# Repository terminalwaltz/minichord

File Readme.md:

# minichord 

This repository contains the source file both for the minichord itself and its documentation. 

To be informed about the project, please subscribe to [the newsletter](https://buttondown.com/BenjaminPoilve).

* [#1 project update](https://buttondown.com/BenjaminPoilve/archive/minichord-update-1/) 
* [#2 project update](https://buttondown.com/BenjaminPoilve/archive/minichord-update-2/) 
* [#3 project update and pre-order link](https://buttondown.com/BenjaminPoilve/archive/minichord-update-3/) 
* [#4 project update](https://buttondown.com/BenjaminPoilve/archive/minichord-update-4/) 
* [#5 project update](https://buttondown.com/BenjaminPoilve/archive/minichord-update-5/) 

## Documentation 

The best way to get to know this project is to visit the [minichord website](https://minichord.com/) which contains the documentation of the project. 

In particular it contains:

- the [user manual of the minichord](https://minichord.com/user_manual/)
- the [assembly guide of the minichord](https://minichord.com/assembly/)

This documentation is build with mkdocs and the relevant source and build script is available in the [documentation folder](https://github.com/BenjaminPoilve/MiniChord/tree/main/documentation).

## Hardware 

The hardware folder contains the necessary ressources to build a minichord. 

All hardware is provided under a Creative Commons Attribution-NonCommercial 4.0 International Public
License (CC BY-NC 4.0). 

In particular it contains: 

- the [files necessary to manufacture the PCB](https://github.com/BenjaminPoilve/MiniChord/tree/main/hardware/PCB)
- the [full BOM of the project](https://github.com/BenjaminPoilve/MiniChord/tree/main/hardware/BOM)
- the [3D enclosure files](https://github.com/BenjaminPoilve/MiniChord/tree/main/hardware/3D/rendering)
- the [keycap routing files](https://github.com/BenjaminPoilve/MiniChord/tree/main/hardware/graphics)

## Firmware 

The firmware folder contains the project firmware and necessary programming ressources.

All software is provided under a 3-clause BSD License.

In particular it contains: 
- the [Hex firmware](https://github.com/BenjaminPoilve/MiniChord/blob/main/firmware/firmware.hex)
- the full [PlatformIO project](https://github.com/BenjaminPoilve/MiniChord/tree/main/firmware)
- the [minicontrol software](https://github.com/BenjaminPoilve/MiniChord/tree/main/firmware/minicontrol)

## Media 

Here is a list of available media related to the project (to be completed) :

- a technical video about [the minicontrol system](https://www.youtube.com/watch?v=h-6qkhU_WoA&t=933s)
- a short [audio demo of selected presets](https://minichord.com/ressources/audio_demo.mp3)

## Contact 

For any information about the project, don't hesitate to write at info@minichord.com

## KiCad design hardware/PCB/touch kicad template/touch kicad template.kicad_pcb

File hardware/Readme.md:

# Hardware  

This folder contains the necessary ressources to build a minichord. 

### Electronics

* [Main PCB schematics](https://github.com/BenjaminPoilve/MiniChord/blob/main/hardware/PCB/miniChord_main_PCB/MiniChord.pdf)
* [Main PCB Gerber file](https://github.com/BenjaminPoilve/MiniChord/tree/main/hardware/PCB/miniChord_main_PCB/gerber)
* [Touch zone PCB schematics](https://github.com/BenjaminPoilve/MiniChord/blob/main/hardware/PCB/touch%20zones/default%20touch%20PCB/touch_zone.pdf)
* [Touch zone PCB Gerber file](https://github.com/BenjaminPoilve/MiniChord/blob/main/hardware/PCB/touch%20zones/default%20touch%20PCB/gerber)
* [Template for custom touch zone](https://github.com/BenjaminPoilve/MiniChord/blob/main/hardware/PCB/touch%20zones/touch%20kicad%20template)

### BOM

* [Full BOM](https://github.com/BenjaminPoilve/MiniChord/blob/main/hardware/BOM/full_BOM.pdf)

### 3D files

* [Bottom shell](https://github.com/BenjaminPoilve/MiniChord/blob/main/hardware/3D/rendering/render_v9_bottom.scad.stl) 
* [Top shell](https://github.com/BenjaminPoilve/MiniChord/blob/main/hardware/3D/rendering/render_v9_top1_5.scad.stl)

### 2D files 

* [Key engraving](https://github.com/BenjaminPoilve/MiniChord/blob/main/hardware/graphics/key_engraving.svg)

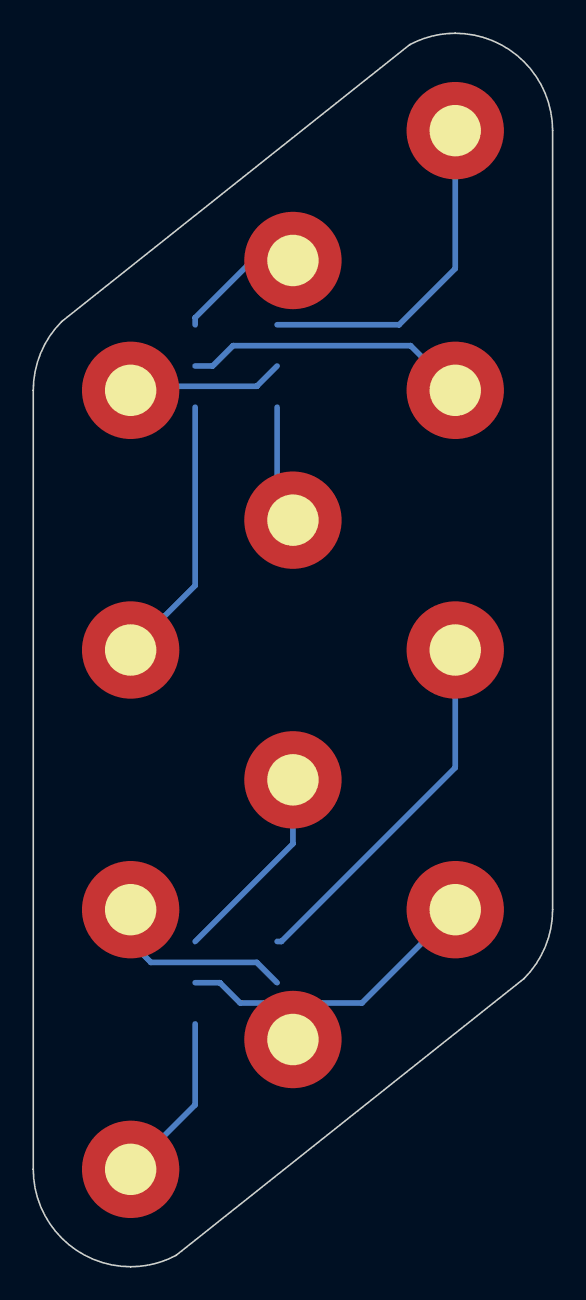
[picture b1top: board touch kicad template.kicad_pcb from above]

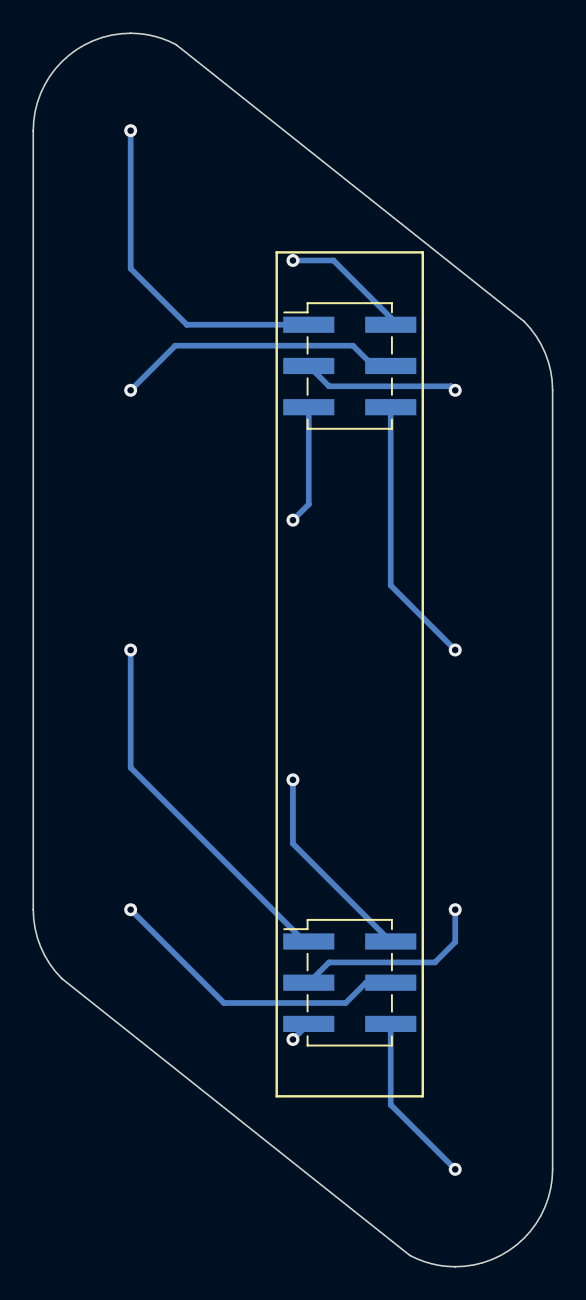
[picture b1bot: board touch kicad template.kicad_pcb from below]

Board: 2 copper layers, 32.0 x 76.0 mm, 14 parts (2 on the bottom side), 12 nets.

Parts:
J1, J2: Conn_02x03_Top_Bottom; PinHeader_2x03_P2.54mm_Vertical_SMD
T1, T2, T3, T4, T5, T6, T7, T8, T9, T10, T11, T12: Conn_01x01_Male; rond_touch_zone

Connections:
unnamed: J1.1, T1.1
unnamed: J1.2, T3.1
unnamed: J1.3, T5.1
unnamed: J1.4, T2.1
unnamed: J1.5, T4.1
unnamed: J1.6, T6.1
unnamed: J2.1, T7.1
unnamed: J2.2, T9.1
unnamed: J2.3, T11.1
unnamed: J2.4, T8.1
unnamed: J2.5, T10.1
unnamed: J2.6, T12.1

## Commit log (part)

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2024-12-26 Additional 3D files, plus
2024-12-26 Added ressources, fixed typo
2024-12-26 Need to clean file uploaded
2024-12-26 fixed a slight bug with regard to pot secondary functions after preset change (caused the pot to updateat the first # selection)
2024-12-30 Small updates and file cleaning
2025-01-07 Added better logging on minicontrol to help diagnose Shiftr's issue
2025-01-08 Made minicontrol windows-compliant and more robust to deconnnections
2025-01-08 Cleaned the connection logic for minicontrol
2025-01-09 Finally tracked down the issue: Dutch locale changing port into poort. Let's be more souple
2025-01-17 Modified firmware for the 10 minichords: better preset, and fixed reverb noise issue
2025-01-17 Updated documentations for new enclosure that necessitates less manual intervention and cutting. Also fixed an error pointed out by Zach
2025-01-17 Annd forgot to build the site
2025-01-17 Better resolution
2025-02-03 Forgot to reactivate the low battery blinking
2025-02-04 Test to try to solve issue #10
2025-02-07 Added Kicad template for custom touch zone
2025-02-07 A bit of housekeeping
2025-02-07 Midi Sync in feature, as requested in #11
2025-02-09 Update on the webpage to reflect the current status of the projetc (production TBD)
2025-02-11 Commiting new homepage
2025-02-11 A bit better design
2025-02-11 hopefully last fix
2025-02-14 at the request of instalinu, added an electronic BOM with MFR#
2025-02-16 Added battery check at startup plus slight deepening of the screw holes
2025-02-17 Changed the touch zone size following Hainbach's feedback
2025-02-17 Added the newsletter issue #2
2025-02-27 Added step rendering
2025-04-11 PCB update to add the diodes
2025-04-11 Latext compile of the firmware
2025-04-11 update doc to acknowledge release
2025-04-11 Better with a break
2025-05-06 Updated PNG of schematics
2025-05-13 Update to reflect the fact that when testing led can be both color
2025-05-23 added chromatic harp flag
2025-06-06 Solve for issue #23 and #22. Had to add a version identifier to avoid user wondering why some control would not work for their version of the firmware.
2025-06-06 Added function for #20.
2025-06-06 Solved issue #21. Could not preserve preset compatibility, need to add a step to wipe preset after software update
2025-06-06 New firmware and new minicontrol interface to take changes into account
2025-06-06 Ressources
2025-06-08 Added documentation on the arrow per #28, plus limited the range of the retrigger release in the frontend per #31 until I can find a better fix
2025-06-13 Reformated the js to have a separate module for minichord interaction. Added a new test page for preset sharing.
2025-06-13 Forgot to build the doc
2025-06-13 Fix for error #29, detecting the loss of USB connection
2025-06-13 new firmware with mods
2025-06-13 Fix for a regression that took the reverb to a very low level
2025-06-15 New updates on the minishop page
2025-06-15 Add underline to parameter name for more legibility
2025-06-15 fixing manual error identified in #32
2025-06-16 Cleanup before PR study
2025-06-16 Fixed for retrocompatibility plus added forgotten JSON modifications
2025-06-18 Added the Barry Harris preset
2025-06-19 Added new issues of the newsletter
2025-06-20 Added feature requested by #25
2025-06-20 Allows global transposition downwards through some dirty math functions (mapNegativeTransposition). Makes changes to handlechange function. Shouldn't break existing presets.
2025-06-22 Fixes loss of MIDI CH2 output when harp pot is set to zero
2025-06-22 Fixes loss of MIDI CH2 output when harp pot is set to zero. Now with firmware.hex to match.
2025-06-24 add 3d files for keycaps
2025-06-25 Added a bit of volume for the transient
2025-06-25 Fixed #42 by removing arbitrary waveforms
2025-06-25 And the
2025-06-25 Here is the new firmware
2025-06-29 Added latest submitted presets
2025-06-30 Adds single/double tap functions to the sharp button. Currently wired for leslie b3, needs parameter assignments, json entries.
2025-07-03 Adds 'chord frame shift' at address 18. Octave array is the reverse of what would be expected, but it works
2025-07-03 Adds JSON entry
2025-07-03 Adds firmware.hex
2025-07-03 Fixing outdated files, bad at GitHub
2025-07-03 Added John's great presets
2025-07-03 added more docs and videos
2025-07-03 Added minishop reference in minicontrol
2025-07-03 Adds 'chord frame shift' at address 18
2025-07-05 Some new presets from Terminalwaltz
2025-07-08 Adds special harp array for Barry Harris mode with a keymaster
2025-07-08 Fixes my presets; my custom firmwareand/or minicontrol experiment added pitch bends unintentionally. I'll be more careful in the future!
2025-07-08 Remove "chord frame shift" from parameters.json
    I promise I will get better at this. Tried to amend from the command line, but I'm missing something clearly. Obviously this is an artifact from another feature, not meant to have altered the JSON fo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
2025-07-08 Adds special harp array for Barry Harris mode with a Keymaster touchplate.
2025-07-10 Adds Chord Frame Shift, with 2D root_button array. Firmware.hex, JSON change, sysex_handler change, address 18
2025-07-10 Forgot to run generator.py
2025-07-11 A new array
2025-07-11 And the corresponding firmware
2025-07-13 Adds support for Key Center; sysex address 35, root_button now a 3D array
2025-07-13 Added random generator to minicontrol
2025-07-13 Drops 3D array, generates proper arrays for root_button in get_root_note()
2025-07-13 Compile after merging with feature-KeyOf
2025-07-13 Some work done, not working yet
2025-07-13 Cleaned up comments, some names for clarity
2025-07-13 Cleaned up some experimental harp code, sorry!
2025-07-14 Overhauled the preset generator, relying on gaussian distribution around center values
2025-07-14 Base random generator not only on default but also on all submitted presets
2025-07-14 Adds 'scalar_harp_selection', allowing harp to be set to scales based on chosed key signature
2025-07-14 Reordered scales to match normal modal order
2025-07-14 max_value changed to 9
2025-07-14 'group' changed to 'General', added Pentatonic Minor (10)
2025-07-14 Fixed scale_lengths array for minor pentatonic
2025-07-14 Adds Relative Natural/Harmonic Minor options to keep chords in their proper key, but still access the minor scale
2025-07-15 More reasonable list of scales (7)
2025-07-15 'note + 24' to 'note' to bring scales down two octaves
2025-07-15 Works! But a bit ugly, cleanup coming...
2025-07-15 Adjusting generate.py to dump parameter_lookup in the potentiometer directory (not ideal)
2025-07-15 firmware.hex
2025-07-16 Now respects percent range scaling for discrete parameters
2025-07-16 firmware.hex t(>.<t)
2025-07-16 Removing updates from feature-ScalarHarpArray to try to keep this clean
2025-07-16 Some work done, not functional yet
2025-07-16 Some more work done, maybe merge with feature-FixPotOverflow, currently sysex_adress=32 pot control outputs only 0
2025-07-16 Adds a lower bound option to potentiometer percent ranges. Builds upon feature-FixPotOverflow
2025-07-16 Fixes scaling for discrete parameters, respects user input
2025-07-16 Improved logic for discretes
2025-07-16 Fixes logic that reversed alternate percent range behavior, i.e. range 0-10 resulted in output 90-100 instead of 0-10.
2025-07-16 Fixes Relative Minor edge case, removes negative integers from scale arrays and deals with those scales downstream
2025-07-16 Works, but some scales are in the wrong octave +/- 1
2025-07-17 testing custom scale option
2025-07-17 Adds 'scale per chord' mode, select scalar harp mode 7
2025-07-17 Now located at scalar harp mode 8, retooled Barry Harris scales for their chords
2025-07-17 Adjusted tooltips
2025-07-19 Some work done, not yet functioning as intended
2025-07-19 Works! Needs tweaking
2025-07-19 Some tweaking, need to fix repeat notes on some scales on double-tap
2025-07-20 Tightening up double-tap scale reset
2025-07-20 Works pretty well, but breaks sharp button
2025-07-20 Adds Scalar Harp Mode 9, pentatonics instead of diatonics, better for strumplate
2025-07-20 Adds Mode 9 (pentatonic), firmware.hex
2025-07-20 Culled Dorian by mistake, adding back
2025-07-20 Now respects rhythm mode
2025-07-20 Fixes handling of augmented/whole tone
2025-07-21 Revert "Fixes handling of augmented/whole tone". Fix was uglier than original problem. Aug presented a unique edge-case This reverts commit 979abe9415fd57f26f953477d9818f0df3959260.
2025-07-21 Fixes Aug edge case. Introduces 'harp_chord' latched to 'current_chord' but won't reset when current_line = -1
2025-07-21 removed errant else block
2025-07-21 ran generate.py
2025-07-24 Adds Master Tuning feature to allow recalibrating notes from 432Hz up to 444Hz.
2025-07-24 Adds Dark Mode toggle to minicontrol
2025-07-24 Rehides 'hidden' parameters
2025-07-25 Adjusts the offset diminished 6th scale
2025-07-26 Alters serialize() and deserialize() to skip reading/writing address 255
2025-07-26 More inconspicuous formatting
2025-07-29 First commit to save progress
2025-07-29 Saving
2025-07-29 Saving, kinda works
2025-07-29 Works, needs UI addition
2025-07-29 UI button works, need formatting, reset_to_user function
2025-07-29 Working user/factory all set, need minicontrol formatting for bubble notification
2025-07-29 Some formatting done
2025-07-29 Good formatting?
2025-07-30 First commit, seems to work
2025-07-30 More reliable key changes, but preset change broken
2025-07-31 Fixes normal preset function, works?
2025-07-31 Tighter, must use simultaneous pressing
2025-07-31 Changed button combo to rows-based
2025-07-31 Restoring comments
2025-07-31 Now respects continuous mode
2025-08-01 Cleaned up loop(), added 'handleKeySignatureChange() call, reuses KeySig enums
2025-08-01 Restoring comments to debouncer.cpp
2025-08-01 Adds cases to control_command
2025-08-01 Firmware updates for bulk preset fetch/upload
2025-08-02 Bulk upload broken into sequential, not quite working yet
2025-08-02 Saving progress on bulk upload
2025-08-02 Bulk upload working!
2025-08-02 Restores processMIDI handling of 6 byte messages
2025-08-03 Bulk upload AND indiv. param supported, for real this time
2025-08-03 Some encoding irregularities, saving progress...
2025-08-03 Control_Command case 0 needs attention
2025-08-03 Tightening up, saving progress...
2025-08-03 Fixes byte discrepancies for minicontrol v. preset manager
2025-08-04 Fixing latching of aug/dim/m7/M7
2025-08-04 Working on chord logic, better
2025-08-04 Better 'stickiness' of harp_chord. loop() is a bit complex now
2025-08-05 Refactors loop() with helper functions. Clean compile
2025-08-05 Tighter multi-button chord response
2025-08-05 Much more solid multibutton chord handling!
2025-08-06 Tightening up timing
2025-08-06 Respects continuous mode off
2025-08-06 Better slash handling
2025-08-06 Better sharp handling
2025-08-06 Faster single chord button detection
2025-08-06 Fixes slash chords in normal mode
2025-08-06 Reconciles sharp/slash problems
2025-08-06 Fixes stale parameters caused by delimiter mismatch in deserialize()
2025-08-07 Refactors handleChordButtons() with helper functions, restores extension changing on same row, keeps chord window
2025-08-07 Refactoring handleChordButtons() for SPC mode
2025-08-07 Better handling in refactored code
2025-08-07 Commenting out some logs for now
2025-08-07 Removes harp_chord, redundant. Fixes chord tones mode
2025-08-07 Merged and ready for testing
2025-08-08 Re-enabled USB Audio out
2025-08-08 Comment cleanup, version number, chord window to 20ms
2025-08-09 Initial commit. Adds all literal enharmonic key signatures (e.g. E#, A#, Fb)
2025-08-09 Fixes handling of double-sharps and double-flats
2025-08-09 Tightens up the key combo to inhibit preset changes while either up/down are being held
2025-08-10 Modifications to deal with negative MIDI notes when Cb is present
2025-08-10 Continuous mode slash chords slightly broken, saving...
